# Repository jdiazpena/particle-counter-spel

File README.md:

# SUCHAI Particle Counter

This repository collects the hardware designs, Raspberry Pi Pico firmware, and
Raspberry Pi acquisition/postprocessing software used to build and operate a
prototype particle counter.

> **Project status:** prototype and research use. The repository is not yet a
> build-ready release. The plotting pipeline has a known altitude-column
> mismatch, and reproducible build/test environments have not yet been
> recorded. Review [Known issues](docs/known-issues.md) before manufacturing
> hardware or processing measurements.

## System overview

```text
S1223-01 photodiode
    -> analog front end
    -> four thresholds per detector (A and B)
    -> Raspberry Pi Pico pulse counters
    -> I2C
    -> Raspberry Pi Zero 2 acquisition
    -> CSV measurements
    -> TLE orbit propagation
    -> geographic and magnetic plots
```

The comparator board produces eight digital channels. `A1` through `A4` are
the four cumulative threshold outputs for detector A; `B1` through `B4` are
the corresponding outputs for detector B. The Pico counts their rising edges
and exposes eight cumulative 32-bit counters to the Raspberry Pi over I2C.

## Repository layout

```text
hardware/
  analog-front-end/             Photodiode amplifier/interstage KiCad project
  comparator-pico-interface/    Comparator, DAC, power, and Pico KiCad project
firmware/
  pico-particle-counter/        RP2040/Arduino pulse-counter firmware
software/
  raspberry-pi/                 Acquisition, orbit processing, and plotting
docs/
  hardware.md                   Boards, connectors, and signal mapping
  firmware.md                   Pico behavior, pin mapping, and I2C protocol
  raspberry-pi-software.md      Acquisition and postprocessing programs
  data-format.md                Measurement columns and derived products
  known-issues.md               Software, reproducibility, and portability limits
```

## Documentation

- [Hardware and wiring](docs/hardware.md)
- [Pico firmware](docs/firmware.md)
- [Raspberry Pi software](docs/raspberry-pi-software.md)
- [Data format](docs/data-format.md)
- [Known issues](docs/known-issues.md)

## Typical workflow

1. Review the schematics, run KiCad ERC/DRC, and assemble and verify the analog
   front end and comparator/interface boards.
2. Flash the Pico with
   [`pico_particle_counter.ino`](firmware/pico-particle-counter/pico_particle_counter.ino).
3. Connect the Pico and MCP4728 to the Raspberry Pi I2C bus.
4. Set the desired threshold voltages in
   [`MCPleves.txt`](software/raspberry-pi/MCPleves.txt).
5. Record detector A, detector B, or both using the corresponding acquisition
   script in [`software/raspberry-pi`](software/raspberry-pi).
6. Add suitable TLE files and run the orbit-cache postprocessor.
7. After addressing the documented `alt_km`/`alt` issue, generate geographic
   and magnetic-coordinate plots.

Detailed commands, paths, dependencies, and output descriptions are in the
linked documents. There is currently no published voltage-to-particle-energy
calibration, so threshold-difference products must not be described as
calibrated energy bins.

## Contributing changes

Keep hardware, firmware, and software revisions traceable. When changing a
board, record whether the schematic or PCB was the starting authority, update
both, run KiCad ERC/DRC, and document the tested physical revision. Avoid
committing KiCad lock/session/cache files or Python bytecode.

## License

No license has been added yet. Until the project owners select one, the files
should not be assumed to grant permission for redistribution or reuse.

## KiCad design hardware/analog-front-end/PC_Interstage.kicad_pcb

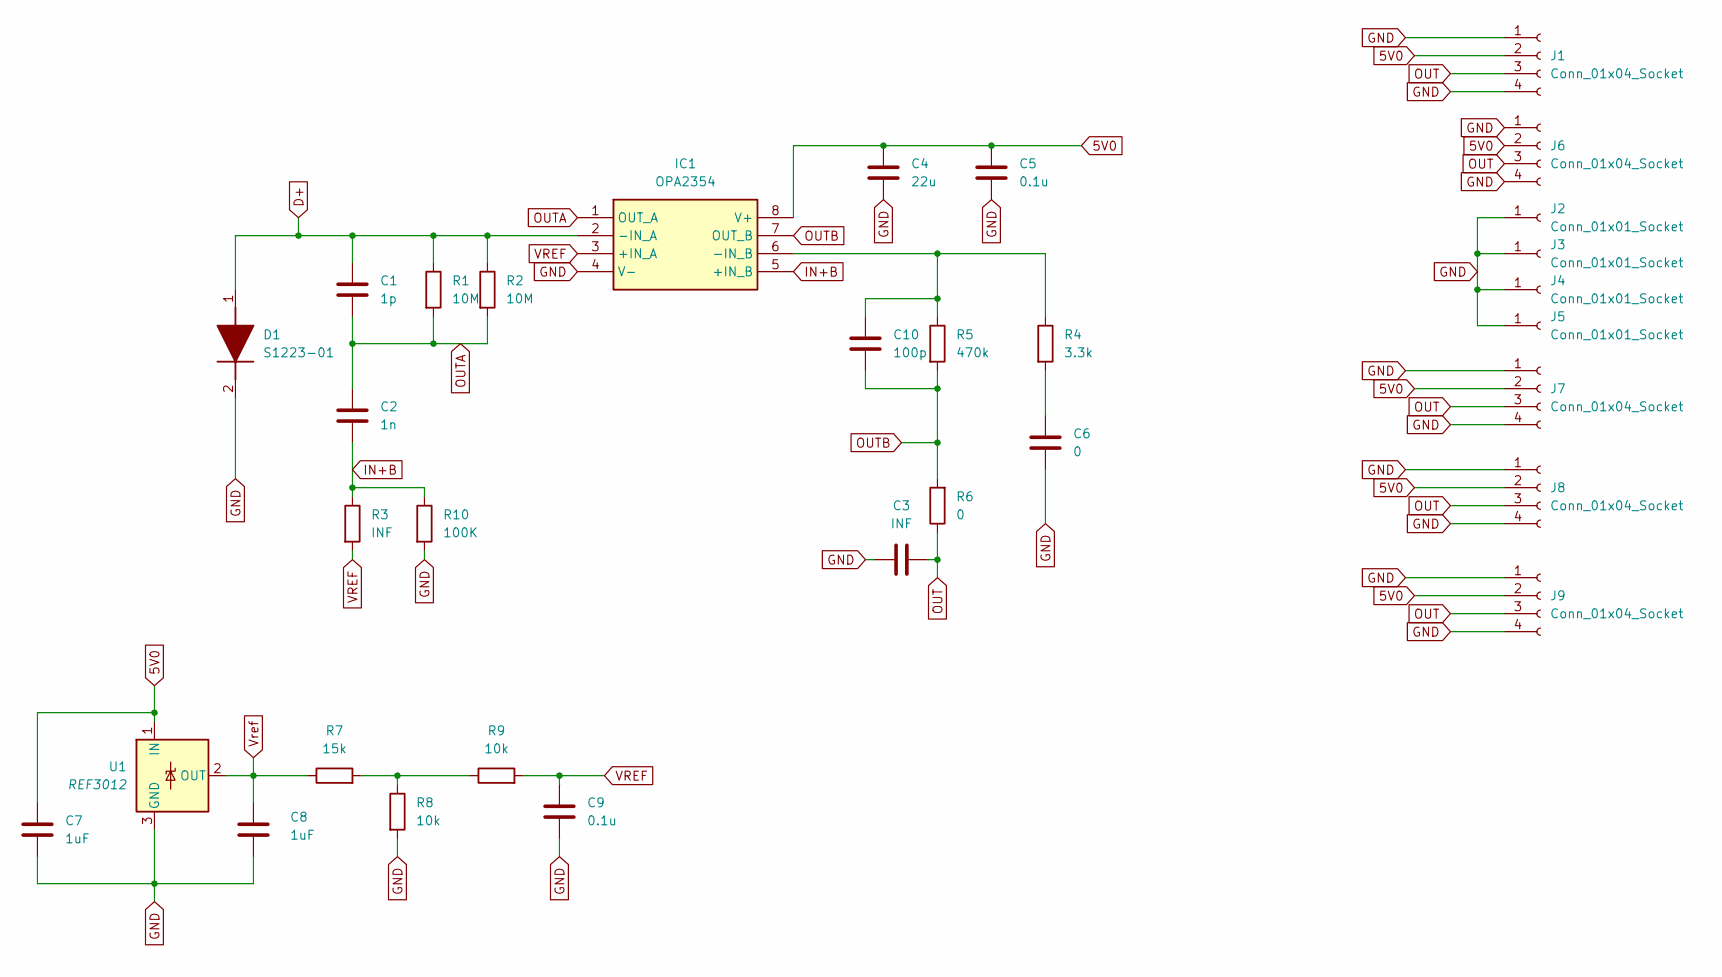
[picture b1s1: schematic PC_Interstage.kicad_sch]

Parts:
C1: 1p; C_0805_2012Metric
C2: 1n; C_0805_2012Metric
C3: INF; C_0805_2012Metric
C4: 22u; C_0805_2012Metric
C5, C9: 0.1u; C_0805_2012Metric
C6: 0; C_0805_2012Metric
C7, C8: 1uF; C_0805_2012Metric
C10: 100p; C_0805_2012Metric
D1: S1223-01; Manufacturer_Part_Number S1223-01
IC1: OPA2354; SOIC127P600X175-8N; Manufacturer_Part_Number OPA1678IDR; Mouser Part Number 595-OPA1678IDR
J1, J7, J8, J9: Conn_01x04_Socket; Molex_Pico-Lock_504050-0491_1x04-1MP_P1.50mm_Horizontal
J2, J3, J4, J5: Conn_01x01_Socket; PinHeader_1x01_P2.54mm_Vertical
J6: Conn_01x04_Socket; PinHeader_1x04_P2.54mm_Vertical
R1: 10M; R_0805_2012Metric
R2: 10M; R_1206_3216Metric_Pad1.30x1.75mm_HandSolder
R3: INF; R_0805_2012Metric
R4: 3.3k; R_0805_2012Metric
R5: 470k; R_0805_2012Metric
R6: 0; R_0805_2012Metric
R7: 15k; R_0805_2012Metric
R8, R9: 10k; R_0805_2012Metric
R10: 100K; R_0805_2012Metric
U1: REF3012; SOT-23

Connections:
5V0: C4.1, C5.1, C7.1, IC1.8 (V+), J1.2, J6.2, J7.2, J8.2, J9.2, U1.1 (IN)
D+: C1.1, D1.1 (A), IC1.2 (-IN_A), R1.1, R2.1
GND: C3.2, C4.2, C5.2, C6.2, C7.2, C8.2, C9.2, D1.2 (K), IC1.4 (V-), J1.1, J1.4, J2.1, J3.1, J4.1, J5.1, J6.1, J6.4, J7.1, J7.4, J8.1, J8.4, J9.1, J9.4, R8.2, R10.2, U1.3 (GND)
IN+B: C2.2, IC1.5 (+IN_B), R3.1, R10.1
unnamed: C6.1, R4.2
unnamed: C10.1, IC1.6 (-IN_B), R4.1, R5.1
unnamed: R7.2, R8.1, R9.1
OUT: C3.1, J1.3, J6.3, J7.3, J8.3, J9.3, R6.1
OUTA: C1.2, C2.1, IC1.1 (OUT_A), R1.2, R2.2
OUTB: C10.2, IC1.7 (OUT_B), R5.2, R6.2
VREF: C9.1, IC1.3 (+IN_A), R3.2, R9.2
Vref: C8.1, R7.1, U1.2 (OUT)

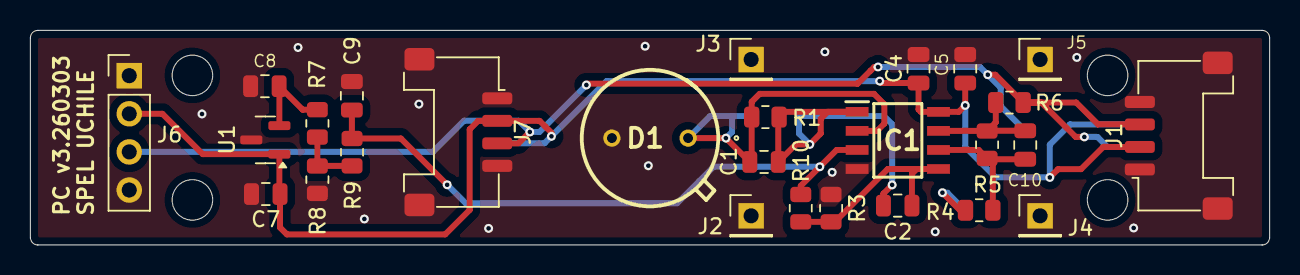
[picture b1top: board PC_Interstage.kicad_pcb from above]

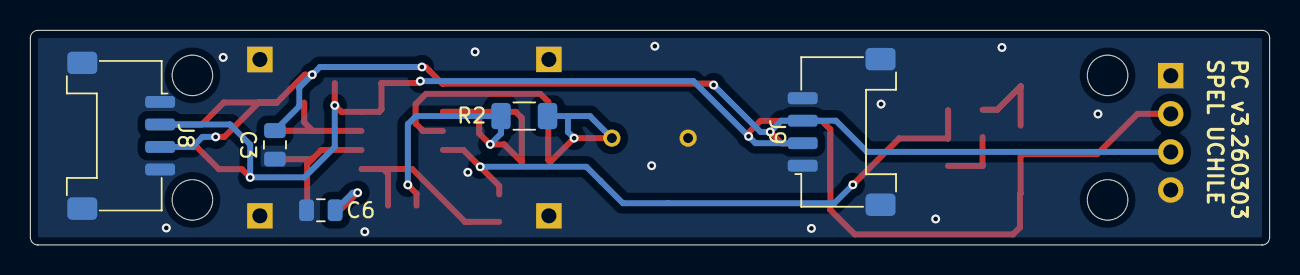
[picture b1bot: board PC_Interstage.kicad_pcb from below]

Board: 2 copper layers, 82.6 x 14.3 mm, 32 parts (5 on the bottom side), 12 nets.

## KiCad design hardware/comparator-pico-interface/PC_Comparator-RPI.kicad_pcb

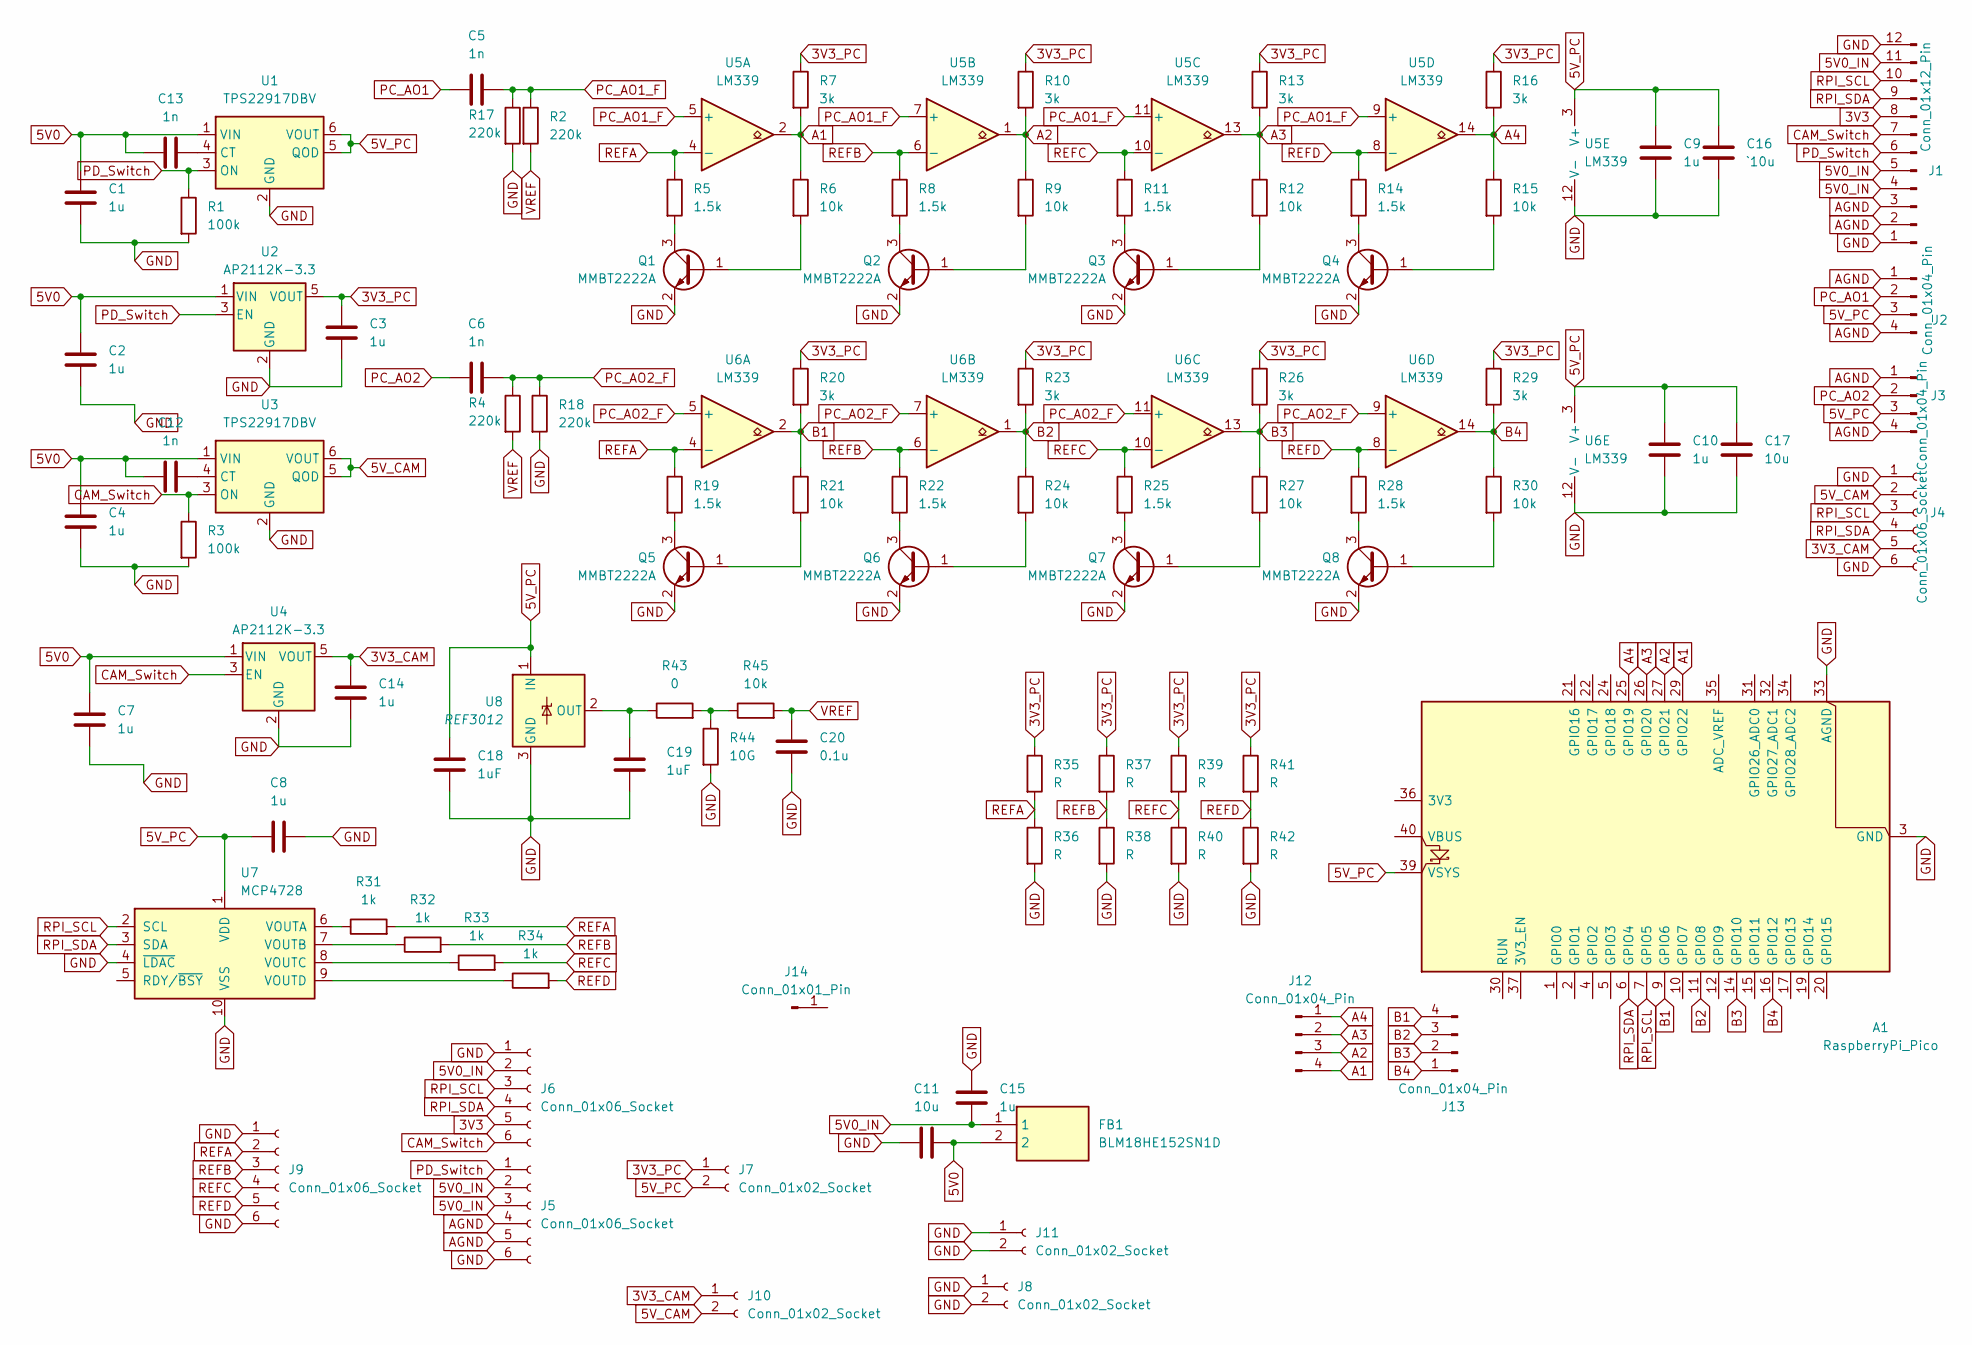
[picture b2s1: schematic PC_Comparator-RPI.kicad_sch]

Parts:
A1: RaspberryPi_Pico; RaspberryPi_Pico_Common_Unspecified
C1, C2, C3, C4, C7, C8, C9, C10, C14, C15: 1u; C_0805_2012Metric_Pad1.18x1.45mm_HandSolder
C5, C6, C12, C13: 1n; C_0805_2012Metric_Pad1.18x1.45mm_HandSolder
C11, C17: 10u; C_0805_2012Metric_Pad1.18x1.45mm_HandSolder
C16: `10u; C_0805_2012Metric_Pad1.18x1.45mm_HandSolder
C18, C19: 1uF; C_0805_2012Metric
C20: 0.1u; C_0805_2012Metric
FB1: BLM18HE152SN1D; BLM18SP221SN1B; Manufacturer_Part_Number BLM18HE152SN1D; Mouser Part Number 81-BLM18HE152SN1D
J1: Conn_01x12_Pin; 5040501291
J2, J3: Conn_01x04_Pin; Molex_Pico-Lock_504050-0491_1x04-1MP_P1.50mm_Horizontal
J4: Conn_01x06_Socket; Molex_Pico-Lock_504050-0691_1x06-1MP_P1.50mm_Horizontal
J5, J6, J9: Conn_01x06_Socket; PinSocket_1x06_P2.54mm_Vertical
J7, J8, J10, J11: Conn_01x02_Socket; PinHeader_1x02_P2.54mm_Vertical
J12, J13: Conn_01x04_Pin; PinHeader_1x04_P2.54mm_Vertical
J14: Conn_01x01_Pin; PinSocket_1x01_P2.54mm_Vertical
Q1, Q2, Q3, Q4, Q5, Q6, Q7, Q8: MMBT2222A; SOT-23
R1, R3: 100k; R_0805_2012Metric_Pad1.20x1.40mm_HandSolder
R2, R4, R17, R18: 220k; R_0805_2012Metric_Pad1.20x1.40mm_HandSolder
R5, R8, R11, R14, R19, R22, R25, R28: 1.5k; R_0805_2012Metric_Pad1.20x1.40mm_HandSolder
R6, R9, R12, R15, R21, R24, R27, R30: 10k; R_0805_2012Metric_Pad1.20x1.40mm_HandSolder
R7, R10, R13, R16, R20, R23, R26, R29: 3k; R_0805_2012Metric_Pad1.20x1.40mm_HandSolder
R31, R32, R33, R34: 1k; R_0805_2012Metric_Pad1.20x1.40mm_HandSolder
R35, R36, R37, R38, R39, R40, R41, R42: R; R_0805_2012Metric_Pad1.20x1.40mm_HandSolder
R43: 0; R_0805_2012Metric
R44: 10G; R_0805_2012Metric
R45: 10k; R_0805_2012Metric
U1, U3: TPS22917DBV; SOT-23-6
U2, U4: AP2112K-3.3; SOT-23-5
U5, U6: LM339; SO-14_5.3x10.2mm_P1.27mm
U7: MCP4728; MSOP-10_3x3mm_P0.5mm
U8: REF3012; SOT-23

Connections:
3V3: J1.8, J6.5
3V3_CAM: C14.1, J4.5, J10.1, U4.5 (VOUT)
3V3_PC: C3.1, J7.1, R7.1, R10.1, R13.1, R16.1, R20.1, R23.1, R26.1, R29.1, R35.1, R37.1, R39.1, R41.1, U2.5 (VOUT)
5V0: C1.1, C2.1, C4.1, C7.1, C11.1, C12.1, C13.1, FB1.2, U1.1 (VIN), U2.1 (VIN), U3.1 (VIN), U4.1 (VIN)
5V0_IN: C15.2, FB1.1, J1.4, J1.5, J1.11, J5.2, J5.3, J6.2
5V_CAM: J4.2, J10.2, U3.5 (QOD), U3.6 (VOUT)
5V_PC: A1.39 (VSYS), C8.2, C9.1, C10.1, C16.1, C17.1, C18.1, J2.3, J3.3, J7.2, U1.5 (QOD), U1.6 (VOUT), U5.3 (V+), U6.3 (V+), U7.1 (VDD), U8.1 (IN)
A1: A1.29 (GPIO22), J12.4, R6.1, R7.2, U5.2
A2: A1.27 (GPIO21), J12.3, R9.1, R10.2, U5.1
A3: A1.26 (GPIO20), J12.2, R12.1, R13.2, U5.13
A4: A1.25 (GPIO19), J12.1, R15.1, R16.2, U5.14
AGND: J1.2, J1.3, J2.1, J2.4, J3.1, J3.4, J5.4, J5.5
B1: A1.9 (GPIO6), J13.4, R20.2, R21.1, U6.2
B2: A1.11 (GPIO8), J13.3, R23.2, R24.1, U6.1
B3: A1.14 (GPIO10), J13.2, R26.2, R27.1, U6.13
B4: A1.16 (GPIO12), J13.1, R29.2, R30.1, U6.14
CAM_Switch: J1.7, J6.6, R3.1, U3.3 (ON), U4.3 (EN)
GND: A1.3 (GND), A1.8 (GND), A1.13 (GND), A1.18 (GND), A1.23 (GND), A1.28 (GND), A1.33 (AGND), A1.38 (GND), C1.2, C2.2, C3.2, C4.2, C7.2, C8.1, C9.2, C10.2, C11.2, C14.2, C15.1, C16.2, C17.2, C18.2, C19.2, C20.2, J1.1, J1.12, J4.1, J4.6, J5.6, J6.1, J8.1, J8.2, J9.1, J9.6, J11.1, J11.2, Q1.2 (E), Q2.2 (E), Q3.2 (E), Q4.2 (E), Q5.2 (E), Q6.2 (E), Q7.2 (E), Q8.2 (E), R1.2, R3.2, R17.2, R18.2, R36.2, R38.2, R40.2, R42.2, R44.2, U1.2 (GND), U2.2 (GND), U3.2 (GND), U4.2 (GND), U5.12 (V-), U6.12 (V-), U7.4 (~LDAC), U7.10 (VSS), U8.3 (GND)
unnamed: Q1.1 (B), R6.2
unnamed: Q1.3 (C), R5.2
unnamed: Q2.1 (B), R9.2
unnamed: Q2.3 (C), R8.2
unnamed: Q3.1 (B), R12.2
unnamed: Q3.3 (C), R11.2
unnamed: Q4.1 (B), R15.2
unnamed: Q4.3 (C), R14.2
unnamed: Q5.1 (B), R21.2
unnamed: Q5.3 (C), R19.2
unnamed: Q6.1 (B), R24.2
unnamed: Q6.3 (C), R22.2
unnamed: Q7.1 (B), R27.2
unnamed: Q7.3 (C), R25.2
unnamed: Q8.1 (B), R30.2
unnamed: Q8.3 (C), R28.2
unnamed: R43.2, R44.1, R45.1
unnamed: C13.2, U1.4 (CT)
unnamed: C12.2, U3.4 (CT)
unnamed: R31.1, U7.6 (VOUTA)
unnamed: R32.1, U7.7 (VOUTB)
unnamed: R33.1, U7.8 (VOUTC)
unnamed: R34.1, U7.9 (VOUTD)
unnamed: C19.1, R43.1, U8.2 (OUT)
PC_AO1: C5.2, J2.2
PC_AO1_F: C5.1, R2.1, R17.1, U5.5 (+), U5.7 (+), U5.9 (+), U5.11 (+)
PC_AO2: C6.2, J3.2
PC_AO2_F: C6.1, R4.1, R18.1, U6.5 (+), U6.7 (+), U6.9 (+), U6.11 (+)
PD_Switch: J1.6, J5.1, R1.1, U1.3 (ON), U2.3 (EN)
REFA: J9.2, R5.1, R19.1, R31.2, R35.2, R36.1, U5.4 (-), U6.4 (-)
REFB: J9.3, R8.1, R22.1, R32.2, R37.2, R38.1, U5.6 (-), U6.6 (-)
REFC: J9.4, R11.1, R25.1, R33.2, R39.2, R40.1, U5.10 (-), U6.10 (-)
REFD: J9.5, R14.1, R28.1, R34.2, R41.2, R42.1, U5.8 (-), U6.8 (-)
RPI_SCL: A1.7 (GPIO5), J1.10, J4.3, J6.3, U7.2 (SCL)
RPI_SDA: A1.6 (GPIO4), J1.9, J4.4, J6.4, U7.3 (SDA)
VREF: C20.1, R2.2, R4.2, R45.2

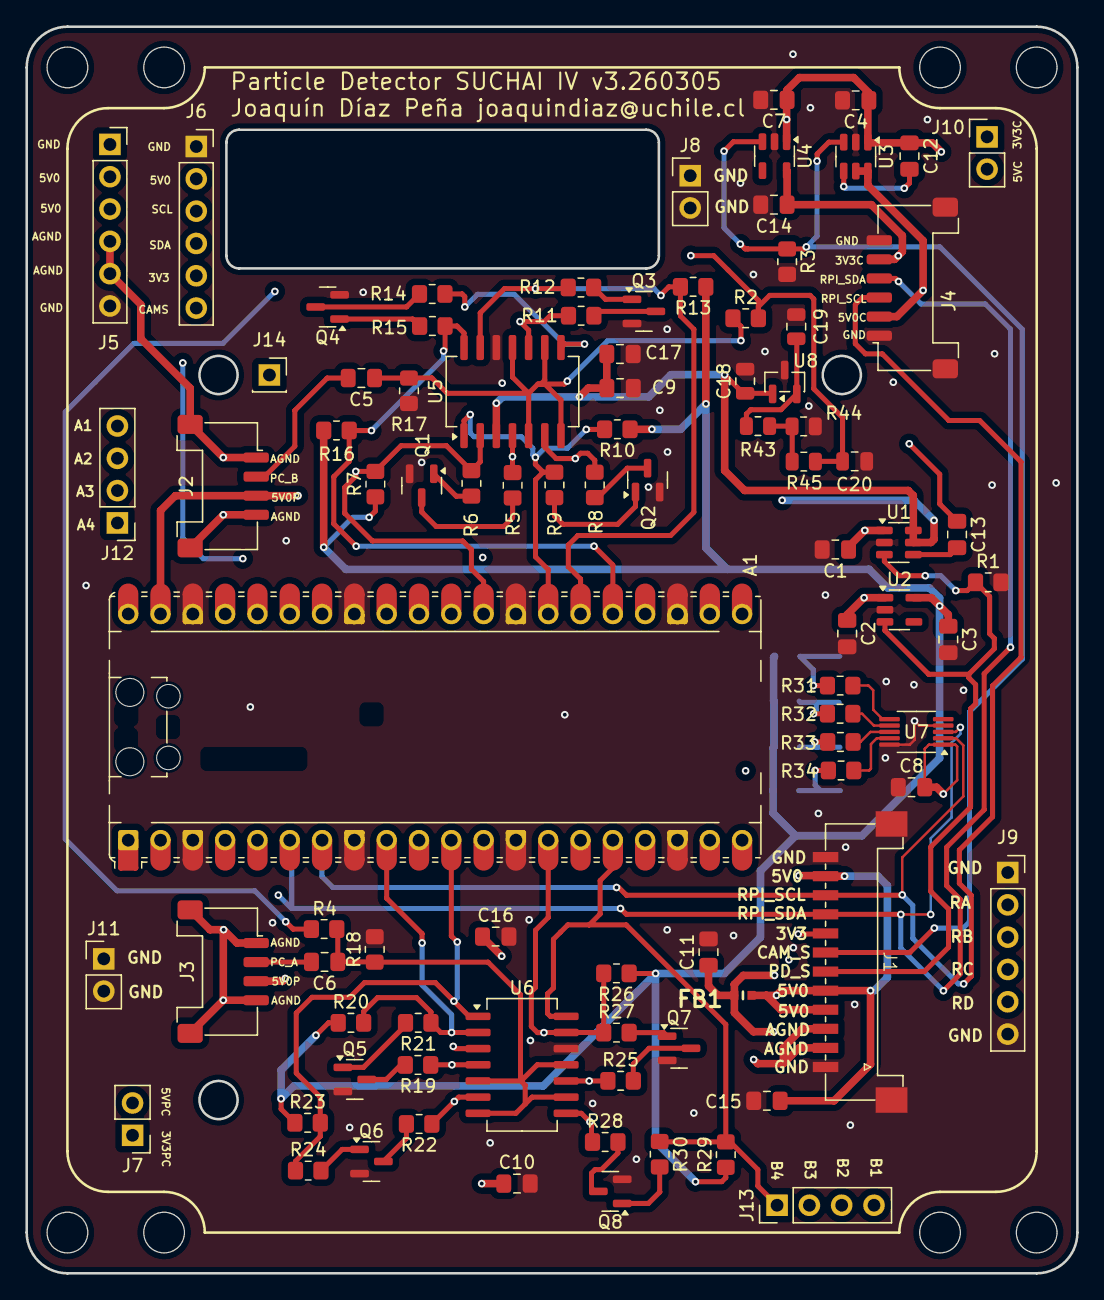
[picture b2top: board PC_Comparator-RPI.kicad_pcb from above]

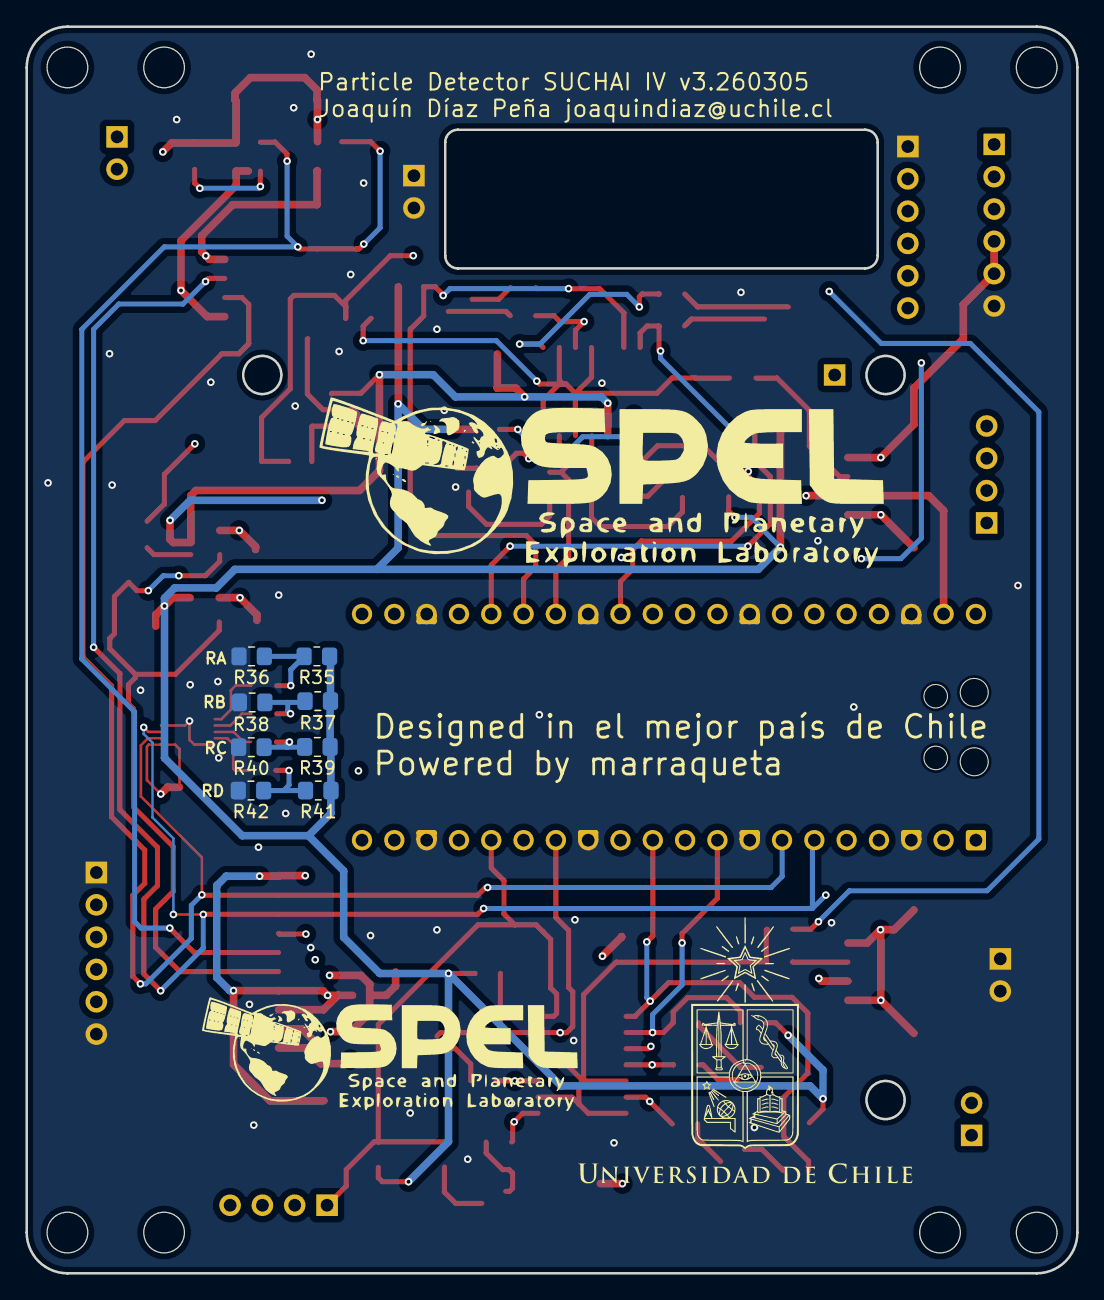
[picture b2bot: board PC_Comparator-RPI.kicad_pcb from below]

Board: 4 copper layers, 82.6 x 98.0 mm, 97 parts (8 on the bottom side), 54 nets.

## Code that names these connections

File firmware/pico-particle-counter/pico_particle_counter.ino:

#include <Arduino.h>
#include <Wire.h>

#include "hardware/pio.h"
#include "hardware/irq.h"
#include "hardware/gpio.h"
#include "hardware/sync.h"
#include "hardware/pio_instructions.h"

#define I2C_ADDR 0x17

#define I2C_SDA 4
#define I2C_SCL 5

// Channel order:
// A1, A2, A3, A4, B1, B2, B3, B4
static const uint8_t CHANNEL_PINS[8] = {
  22,  // A1
  21,  // A2
  20,  // A3
  19,  // A4
   6,  // B1
   8,  // B2
  10,  // B3
  12   // B4
};

volatile uint32_t counters[8] = {0};

// PIO program, written directly as instructions.
// Equivalent to:
//
// .wrap_target
//     wait 0 pin 0
//     wait 1 pin 0
//     irq wait rel 0
// .wrap
//
static const uint16_t pulse_counter_program_instructions[] = {
  (uint16_t)pio_encode_wait_pin(false, 0),
  (uint16_t)pio_encode_wait_pin(true,  0),
  (uint16_t)pio_encode_irq_wait(true, 0)
};

static const struct pio_program pulse_counter_program = {
  .instructions = pulse_counter_program_instructions,
  .length = 3,
  .origin = -1
};

void pack_u32_le(uint8_t *buf, uint32_t value) {
  buf[0] = (value >> 0)  & 0xFF;
  buf[1] = (value >> 8)  & 0xFF;
  buf[2] = (value >> 16) & 0xFF;
  buf[3] = (value >> 24) & 0xFF;
}

void onRequest() {
  uint32_t snapshot[8];
  uint8_t buffer[32];

  uint32_t irq_state = save_and_disable_interrupts();

  for (int i = 0; i < 8; i++) {
    snapshot[i] = counters[i];
  }

  restore_interrupts(irq_state);

  for (int i = 0; i < 8; i++) {
    pack_u32_le(&buffer[4 * i], snapshot[i]);
  }

  Wire.write(buffer, 32);
}

void pio0_irq0_handler() {
  for (int sm = 0; sm < 4; sm++) {
    if (pio_interrupt_get(pio0, sm)) {
      counters[sm]++;
      pio_interrupt_clear(pio0, sm);
    }
  }
}

void pio1_irq0_handler() {
  for (int sm = 0; sm < 4; sm++) {
    if (pio_interrupt_get(pio1, sm)) {
      counters[4 + sm]++;
      pio_interrupt_clear(pio1, sm);
    }
  }
}

void setup_one_counter(PIO pio, uint sm, uint offset, uint gpio) {
  gpio_init(gpio);
  gpio_disable_pulls(gpio);

  pio_gpio_init(pio, gpio);
  pio_sm_set_consecutive_pindirs(pio, sm, gpio, 1, false);

  pio_sm_config c = pio_get_default_sm_config();

  sm_config_set_in_pins(&c, gpio);

  // Program length = 3 instructions.
  // Wrap from instruction offset+2 back to offset+0.
  sm_config_set_wrap(&c, offset + 0, offset + 2);

  pio_sm_init(pio, sm, offset, &c);
  pio_sm_set_enabled(pio, sm, true);
}

void setup_pio_counters() {
  uint offset0 = pio_add_program(pio0, &pulse_counter_program);
  uint offset1 = pio_add_program(pio1, &pulse_counter_program);

  irq_set_exclusive_handler(PIO0_IRQ_0, pio0_irq0_handler);
  irq_set_exclusive_handler(PIO1_IRQ_0, pio1_irq0_handler);

  for (int sm = 0; sm < 4; sm++) {
    pio_set_irq0_source_enabled(pio0, (pio_interrupt_source_t)(pis_interrupt0 + sm), true);
    pio_set_irq0_source_enabled(pio1, (pio_interrupt_source_t)(pis_interrupt0 + sm), true);
  }

  irq_set_enabled(PIO0_IRQ_0, true);
  irq_set_enabled(PIO1_IRQ_0, true);

  setup_one_counter(pio0, 0, offset0, CHANNEL_PINS[0]);  // A1 GPIO22
  setup_one_counter(pio0, 1, offset0, CHANNEL_PINS[1]);  // A2 GPIO21
  setup_one_counter(pio0, 2, offset0, CHANNEL_PINS[2]);  // A3 GPIO20
  setup_one_counter(pio0, 3, offset0, CHANNEL_PINS[3]);  // A4 GPIO19

  setup_one_counter(pio1, 0, offset1, CHANNEL_PINS[4]);  // B1 GPIO6
  setup_one_counter(pio1, 1, offset1, CHANNEL_PINS[5]);  // B2 GPIO8
  setup_one_counter(pio1, 2, offset1, CHANNEL_PINS[6]);  // B3 GPIO10
  setup_one_counter(pio1, 3, offset1, CHANNEL_PINS[7]);  // B4 GPIO12
}

void setup_i2c() {
  Wire.setSDA(I2C_SDA);
  Wire.setSCL(I2C_SCL);

  Wire.begin(I2C_ADDR);
  Wire.onRequest(onRequest);
}

void setup() {
  pinMode(LED_BUILTIN, OUTPUT);

  setup_pio_counters();
  setup_i2c();
}

void loop() {
  digitalWrite(LED_BUILTIN, HIGH);
  delay(100);
  digitalWrite(LED_BUILTIN, LOW);
  delay(900);
}
